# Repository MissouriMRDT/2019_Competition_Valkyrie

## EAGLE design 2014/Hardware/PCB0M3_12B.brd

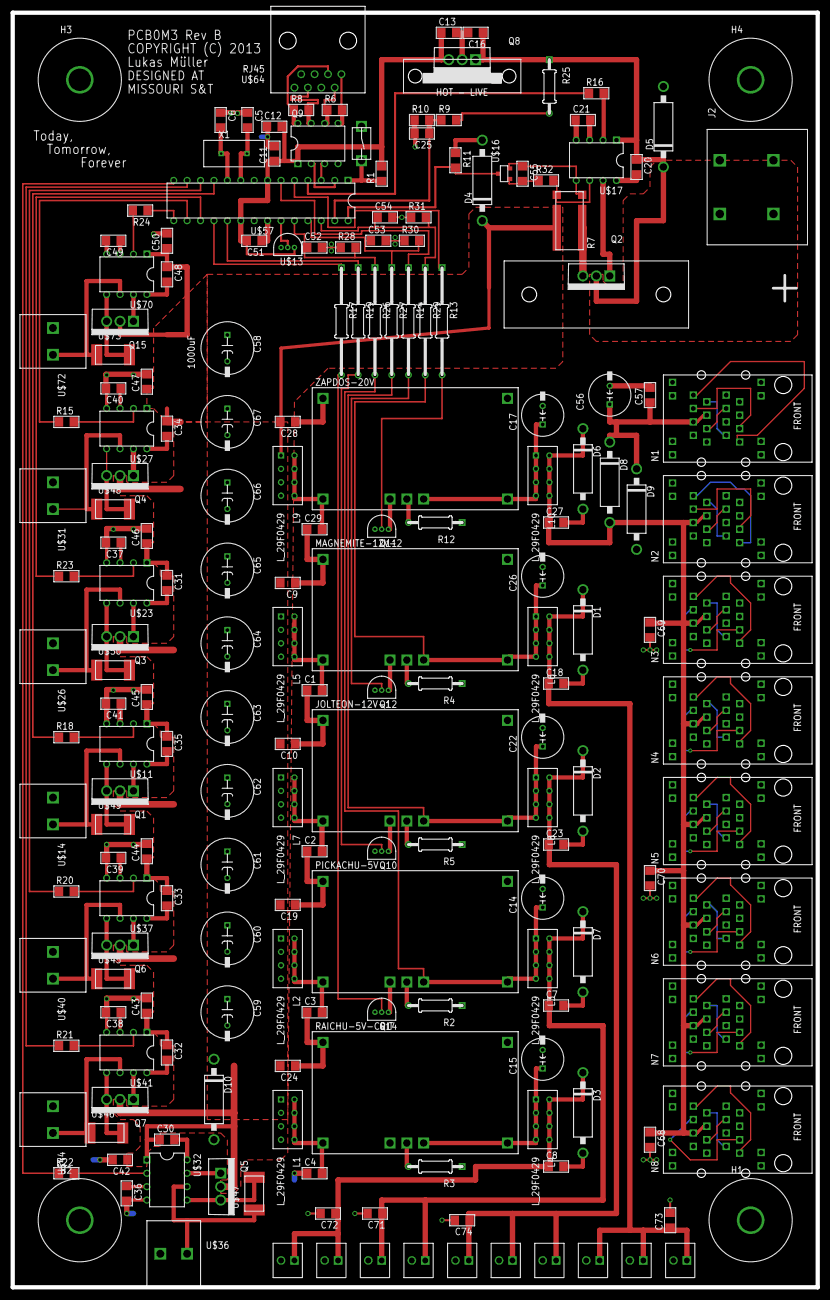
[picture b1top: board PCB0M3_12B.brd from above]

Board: 2 copper layers, 152.4 x 241.3 mm, 196 parts (0 on the bottom side), 143 nets.

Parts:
C1, C2, C3, C4, C5, C6, C11, C12, C13, C16, C20, C21, C25, C29, C30, C31, C32, C33, C34, C35, C36, C37, C38, C39, C40, C41, C42, C43, C44, C45, C46, C47, C48, C49, C50, C51, C52, C53, C54, C55, C57: C_1206
C7, C8, C9, C10, C18, C19, C23, C24, C27, C28, C68, C69, C70, C71, C72, C73, C74: 1uF; C_1206
C14, C15, C17, C22, C26, C56: C_POL8MM; C_8MM
C58: 1000uF; C_10MM
C59, C60, C61, C62, C63, C64, C65, C66, C67: C_10MM
D1, D2: 1.5KE13A-E3/54; DIODE_D3.5MM_LS15.24MM
D3, D7: ICTE5-E3/54; DIODE_D3.5MM_LS15.24MM
D4, D5, D10: 1.5KE30C-RH; DIODE_D3.5MM_LS15.24MM
D6: 1.5KE24CA-E3/73; DIODE_D3.5MM_LS15.24MM
D8, D9: SB530-E3/54; DIODE_D3.5MM_LS15.24MM
H1, H2, H3, H4: H_MNTHOLE_#8
J1: J_MC32857; J_TOGGLE
J2: 0399700102; J_2CONHC
J3, J4, J5, J6, J7, J8: J_1546074-2282834-2; J_2.54MM
JOLTEON-12V-1: PTN78020HAH; R_PDSS-T7
L1, L2, L3, L4, L5, L6, L7, L8, L9, L10: L_29F0429
MAGNEMITE-12V-2: PTN78020HAH; R_PDSS-T7
N1, N2, N3, N4, N5, N6, N7, N8: RJ45; RJ45-CAT5E-2PACK
PICKACHU-5V: PTN78020WAH; R_PDSS-T7
Q1, Q3, Q4, Q5, Q6, Q7, Q15: U_FDPF045N10A_TO-220F; TO220F
Q2: Q_IRFB7437PBF_HS; TO-220-531102B02500G
Q8: Q_LDOHEATSINK; TO220_6025DG
Q9: Q_LTC490; DIP8
Q10, Q11, Q12, Q14: Q_2N7000; TO-92-3
R1, R6, R8, R9, R10, R11, R15, R16, R18, R20, R21, R22, R23, R24, R28, R30, R31, R32: R_1206
R2, R3: 21k; R_1/4W
R4, R5: 242k; R_1/4W
R7: 0.001; R_FC4L
R12: 1.74k; R_1/4W
R13, R14, R17, R19, R26, R27, R29: R_1/4WL
R25: R_1/4W
RAICHU-5V-CRIT: PTN78020WAH; R_PDSS-T7
U$11, U$17, U$23, U$27, U$32, U$37, U$41, U$70: Q_MIC5021; DIP8
U$13: Q_LM35; TO-92-3
U$14, U$26, U$31, U$36, U$40, U$44, U$72: J_1546074-2; THERM_BLOCK_2
U$16: Q_ZXCT1109; SOT23
U$45, U$46, U$47, U$48, U$49, U$50, U$73: R_2512
U$52, U$53, U$54, U$55: J_1546074-2282834-2; J_2.54MM
U$57: Q_ATMEGA328P; DIP28
U$64: RJ45; RJ45-CAT5E
X1: HC49S; HC-49
ZAPDOS-20V: PTN78020HAH; R_PDSS-T7

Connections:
GND: C1.1, C2.1, C3.1, C4.1, C5.1, C6.1, C7.2, C8.2, C9.1, C10.1, C11.2, C12.1, C13.2, C14.-, C15.-, C16.2, C17.-, C18.2, C19.1, C21.1, C22.-, C23.2, C24.1, C25.2, C26.-, C27.2, C28.1, C29.1, C36.2, C37.2, C38.2, C39.2, C40.2, C41.2, C42.2, C43.2, C44.2, C45.2, C46.2, C47.2, C49.2, C50.2, C51.1, C52.2, C53.2, C54.2, C56.-, C57.2, C58.P$2, C59.P$2, C60.P$2, C61.P$2, C62.P$2, C63.P$2, C64.P$2, C65.P$2, C66.P$2, C67.P$2, C68.2, C69.2, C70.2, C71.2, C72.2, C73.2, C74.2, D1.A, D2.A, D3.A, D4.A, D5.A, D6.A, D7.A, D10.A, J1.P$1, J2.PIN2-1, J2.PIN2-2, J3.P$2, J4.P$2, J5.P$2, J6.P$2, J7.P$2, J8.P$2, JOLTEON-12V-1.1, JOLTEON-12V-1.7, MAGNEMITE-12V-2.1, MAGNEMITE-12V-2.7, N1.1-7, N1.1-8, N1.2-7, N1.2-8, N2.1-7, N2.1-8, N2.2-7, N2.2-8, N3.1-7, N3.1-8, N3.2-7, N3.2-8, N4.1-7, N4.1-8, N4.2-7, N4.2-8, N5.1-7, N5.1-8, N5.2-7, N5.2-8, N6.1-7, N6.1-8, N6.2-7, N6.2-8, N7.1-7, N7.1-8, N7.2-7, N7.2-8, N8.1-7, N8.1-8, N8.2-7, N8.2-8, PICKACHU-5V.1, PICKACHU-5V.7, Q8.2, Q9.4, Q10.1, Q11.1, Q12.1, Q14.1, R2.1, R3.1, R4.1, R5.1, R10.1, R11.1, R12.1, R28.1, R30.1, R31.1, RAICHU-5V-CRIT.1, RAICHU-5V-CRIT.7, U$11.4, U$13.1, U$14.P$2, U$17.4, U$23.4, U$26.P$2, U$27.4, U$31.P$2, U$32.4, U$36.P$2, U$37.4, U$40.P$2, U$41.4, U$44.P$2, U$52.P$2, U$53.P$2, U$54.P$2, U$55.P$2, U$57.8, U$57.22, U$64.7, U$64.8, U$70.4, U$72.P$2, ZAPDOS-20V.1, ZAPDOS-20V.7
M_IMAIN: R11.2, U$16.3, U$57.28
M_V5-2: C52.1, R26.1, R28.2, U$57.24
M_V12-1: C53.1, R27.1, R30.2, U$57.25
M_V12-2: C54.1, R29.1, R31.2, U$57.26
M_VMAIN: C25.1, R9.1, R10.2, U$57.27
unnamed: MAGNEMITE-12V-2.4, R4.2
unnamed: C26.+, L6.1, L6.2, L6.3, L6.4, MAGNEMITE-12V-2.5, MAGNEMITE-12V-2.6, R29.2
unnamed: Q14.2, R17.2
unnamed: JOLTEON-12V-1.4, R5.2
unnamed: C22.+, JOLTEON-12V-1.5, JOLTEON-12V-1.6, L8.1, L8.2, L8.3, L8.4, R27.2
unnamed: U$13.2, U$57.23
unnamed: N6.1-1, N6.2-1
unnamed: N6.1-2, N6.2-2
unnamed: N6.1-3, N6.2-3
unnamed: N6.1-6, N6.2-6
unnamed: N5.1-1, N5.2-1
unnamed: N5.1-2, N5.2-2
unnamed: N5.1-3, N5.2-3
unnamed: N5.1-6, N5.2-6
unnamed: N4.1-1, N4.2-1
unnamed: N4.1-2, N4.2-2
unnamed: N4.1-3, N4.2-3
unnamed: N4.1-6, N4.2-6
unnamed: N3.1-1, N3.2-1
unnamed: N3.1-2, N3.2-2
unnamed: N3.1-6, N3.2-6
unnamed: N2.1-1, N2.2-1
unnamed: N2.1-2, N2.2-2
unnamed: N2.1-3, N2.2-3
unnamed: N2.1-6, N2.2-6
unnamed: N1.1-1, N1.2-1
unnamed: N1.1-2, N1.2-2
unnamed: N1.1-3, N1.2-3
unnamed: N1.1-6, N1.2-6
unnamed: N3.1-3, N3.2-3
unnamed: N7.1-1, N7.2-1
unnamed: N7.1-2, N7.2-2
unnamed: N7.1-3, N7.2-3
unnamed: N7.1-6, N7.2-6
unnamed: N8.1-1, N8.2-1
unnamed: N8.1-2, N8.2-2
unnamed: N8.1-3, N8.2-3
unnamed: N8.1-6, N8.2-6
unnamed: Q1.3, U$11.5, U$49.P$2
unnamed: U$11.6, U$14.P$1, U$49.P$1
unnamed: Q1.1, U$11.7
unnamed: R18.2, U$11.2
unnamed: C35.2, U$11.8
unnamed: Q2.1, U$17.7
unnamed: Q2.3, R7.1
unnamed: C55.1, R7.SENSE1, U$16.2, U$17.5
unnamed: R16.2, U$17.2
unnamed: C21.2, U$17.3
unnamed: R3.2, RAICHU-5V-CRIT.4
unnamed: PICKACHU-5V.4, R2.2
unnamed: C55.2, R32.1, U$16.1
unnamed: Q3.3, U$23.5, U$50.P$2
unnamed: C14.+, L3.1, L3.2, L3.3, L3.4, PICKACHU-5V.5, PICKACHU-5V.6, R26.2
unnamed: C15.+, L4.1, L4.2, L4.3, L4.4, RAICHU-5V-CRIT.5, RAICHU-5V-CRIT.6
unnamed: U$23.6, U$26.P$1, U$50.P$1
unnamed: Q3.1, U$23.7
unnamed: C1.2, L5.5, L5.6, L5.7, L5.8, MAGNEMITE-12V-2.2
unnamed: R23.2, U$23.2
unnamed: C31.2, U$23.8
unnamed: Q4.3, U$27.5, U$48.P$2
unnamed: U$27.6, U$31.P$1, U$48.P$1
unnamed: Q4.1, U$27.7
unnamed: R15.2, U$27.2
unnamed: C34.2, U$27.8
unnamed: C3.2, L2.5, L2.6, L2.7, L2.8, PICKACHU-5V.2
unnamed: Q5.3, U$32.5, U$47.P$2
unnamed: U$32.6, U$36.P$1, U$47.P$1
unnamed: Q5.1, U$32.7
unnamed: R22.2, U$32.2
unnamed: C30.2, U$32.8
unnamed: Q6.3, U$37.5, U$45.P$2
unnamed: U$37.6, U$40.P$1, U$45.P$1
unnamed: Q6.1, U$37.7
unnamed: R20.2, U$37.2
unnamed: C33.2, U$37.8
unnamed: Q7.3, U$41.5, U$46.P$2
unnamed: U$41.6, U$44.P$1, U$46.P$1
unnamed: Q7.1, U$41.7
unnamed: R21.2, U$41.2
unnamed: C32.2, U$41.8
unnamed: Q15.3, U$70.5, U$73.P$2
unnamed: C5.2, U$57.9, X1.P$2
unnamed: C6.2, U$57.10, X1.P$1
unnamed: Q9.2, U$57.2
unnamed: R7.SENSE2, R32.2, U$17.6
unnamed: J1.P$2, R1.1, U$57.1
unnamed: Q9.3, U$57.3
unnamed: R12.2, ZAPDOS-20V.4
unnamed: Q9.5, R6.2, U$64.1
unnamed: Q9.6, R6.1, U$64.2
unnamed: Q9.7, R8.2, U$64.6
unnamed: R9.2, R25.2
unnamed: Q9.8, R8.1, U$64.3
unnamed: U$70.6, U$72.P$1, U$73.P$1
unnamed: C20.2, U$17.8
unnamed: C17.+, L10.1, L10.2, L10.3, L10.4, ZAPDOS-20V.5, ZAPDOS-20V.6
unnamed: C29.2, L9.5, L9.6, L9.7, L9.8, ZAPDOS-20V.2
unnamed: JOLTEON-12V-1.3, Q10.3
unnamed: MAGNEMITE-12V-2.3, Q12.3
unnamed: Q11.3, ZAPDOS-20V.3
unnamed: PICKACHU-5V.3, Q14.3
unnamed: C41.1, U$11.3
unnamed: C37.1, U$23.3
unnamed: C36.1, U$32.3
unnamed: C38.1, U$41.3
unnamed: C39.1, U$37.3
unnamed: C40.1, U$27.3
unnamed: C2.2, JOLTEON-12V-1.2, L7.5, L7.6, L7.7, L7.8
unnamed: Q11.2, R13.2
unnamed: C4.2, L1.5, L1.6, L1.7, L1.8, RAICHU-5V-CRIT.2
unnamed: Q10.2, R19.2
unnamed: Q12.2, R14.2
unnamed: Q15.1, U$70.7
unnamed: C48.2, U$70.8
unnamed: C49.1, U$70.3
unnamed: R24.2, U$70.2
S_12V-2: R14.1, U$57.6
S_MAIN: R16.1, U$57.4
S_MC1: R22.1, U$57.14
S_MC2: R21.1, U$57.13
S_MC3: R20.1, U$57.12
S_MC4: R18.1, U$57.11
S_MC5: R15.1, U$57.16
S_MC6: R23.1, U$57.17
S_POE: R13.1, U$57.5
S_V5-2: R17.1, U$57.18
S_V12-1: R19.1, U$57.19
S_V24AUX: R24.1, U$57.15
V1: C16.1, C20.1, D5.C, J2.PIN1-1, J2.PIN1-2, Q2.2, Q8.1, R25.1, U$17.1
V5-CRT: C8.1, C72.1, D3.C, L4.5, L4.6, L4.7, L4.8, U$52.P$1, U$53.P$1
V12: C7.1, C71.1, D7.C, L3.5, L3.6, L3.7, L3.8, U$54.P$1, U$55.P$1
V15_1: C18.1, C73.1, D1.C, J6.P$1, J7.P$1, J8.P$1, L6.5, L6.6, L6.7, L6.8
V15_2: C23.1, C74.1, D2.C, J3.P$1, J4.P$1, J5.P$1, L8.5, L8.6, L8.7, L8.8
V24: C9.2, C10.2, C19.2, C24.2, C28.2, C30.1, C31.1, C32.1, C33.1, C34.1, C35.1, C42.1, C43.1, C44.1, C45.1, C46.1, C47.1, C48.1, C50.1, C58.P$1, C59.P$1, C60.P$1, C61.P$1, C62.P$1, C63.P$1, C64.P$1, C65.P$1, C66.P$1, C67.P$1, D4.C, D10.C, L1.1, L1.2, L1.3, L1.4, L2.1, L2.2, L2.3, L2.4, L5.1, L5.2, L5.3, L5.4, L7.1, L7.2, L7.3, L7.4, L9.1, L9.2, L9.3, L9.4, Q1.2, Q3.2, Q4.2, Q5.2, Q6.2, Q7.2, Q15.2, R7.2, U$11.1, U$23.1, U$27.1, U$32.1, U$37.1, U$41.1, U$70.1
VA5: C11.1, C12.2, C13.1, C51.2, Q8.3, Q9.1, R1.2, U$13.3, U$57.7, U$57.20
V_ANTENNA: C56.+, C57.1, D8.C, D9.C, N1.1-4, N1.1-5
V_POE: C27.1, C68.1, C69.1, C70.1, D6.C, D8.A, L10.5, L10.6, L10.7, L10.8, N2.1-4, N2.1-5, N3.1-4, N3.1-5, N4.1-4, N4.1-5, N5.1-4, N5.1-5, N6.1-4, N6.1-5, N7.1-4, N7.1-5, N8.1-4, N8.1-5

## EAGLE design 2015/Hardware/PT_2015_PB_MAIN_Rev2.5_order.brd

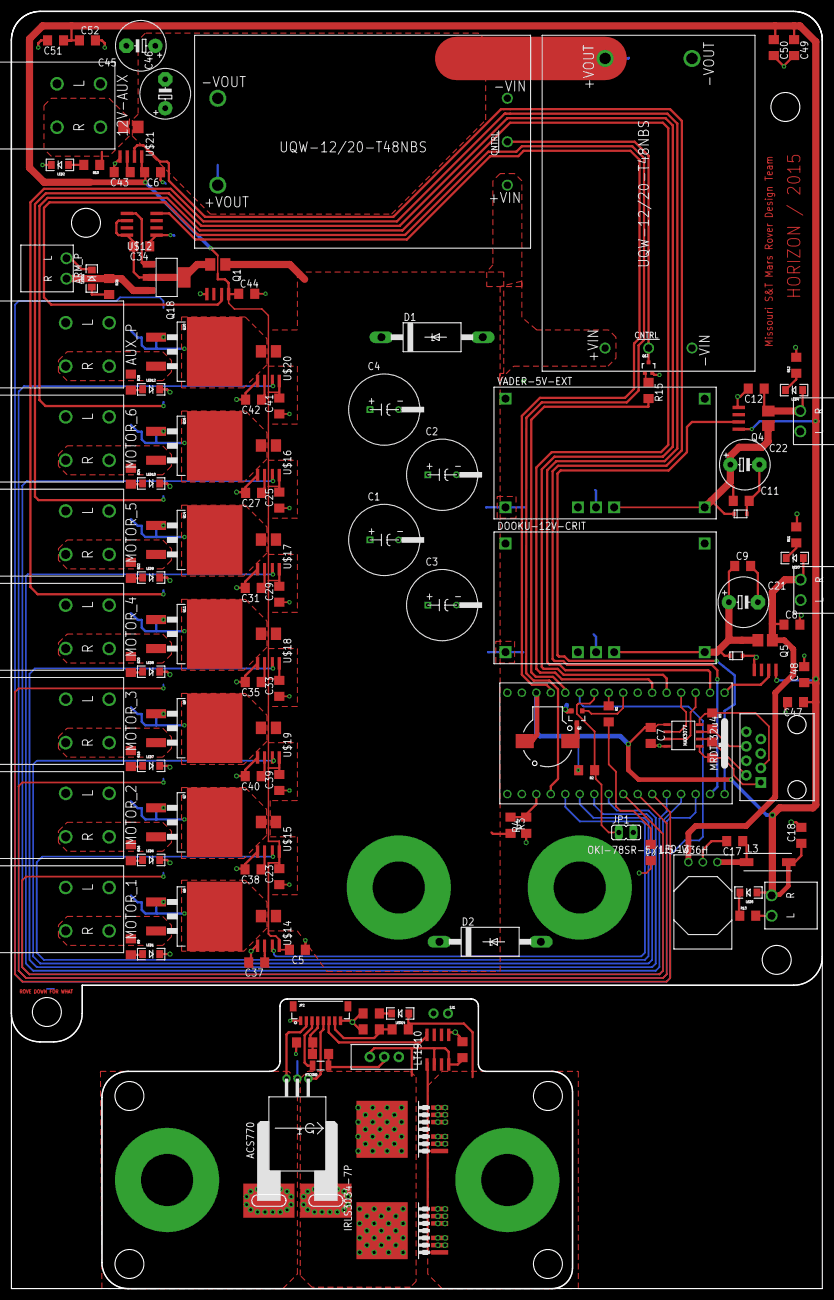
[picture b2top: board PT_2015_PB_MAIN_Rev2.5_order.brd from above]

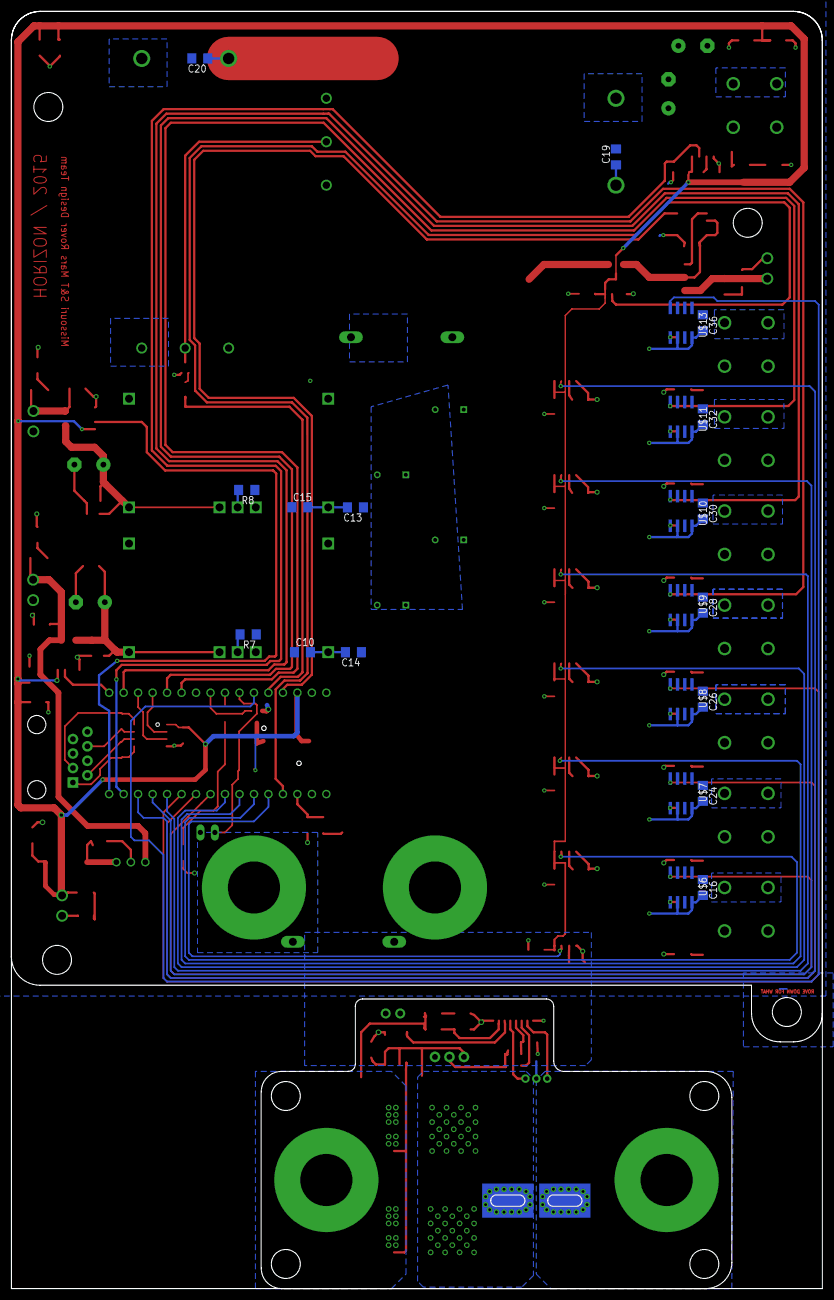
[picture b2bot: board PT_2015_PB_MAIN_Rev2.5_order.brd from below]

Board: 2 copper layers, 142.2 x 224.0 mm, 162 parts (22 on the bottom side), 103 nets.

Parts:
5V-EXT, 5V-INT, 12V-CRIT: H_WR-TBL_321*0002HORIZ; 691322110002
12V-AUX: H_20020618-M02HORIZ; 20020618-M02
ARM_P: H_WR-TBL_321*0002HORIZ; 691322110002
AUX_P: H_20020618-M02HORIZ; 20020618-M02
BATT-NEG: TERMINAL_HOLE; LARGE_TERMINAL_HOLE
BATT-POS: TERMINAL_HOLE; LARGE_TERMINAL_HOLE
C1, C2, C3, C4: 1mF; C_12.5MM
C5, C6, C23, C25, C29, C33, C39, C41, C44: .1µF; C1206
C7: 1uF; C1206
C8: 10µf; C1206
C9, C11, C48, C50, C52: 10uF; C1206
C10, C15, C16, C24, C26, C28, C30, C32, C34, C36, C53: 10µF; C1206
C12: 47µf; C1206
C13, C14: 1µF; C1206
C17, C18: 47µF; C1206
C19, C20: 47uF; C1206
C21, C22, C45, C46: 330µF; E5-8,5
C27, C31, C35, C37, C38, C40, C42, C43, C47, C49, C51: 1nF; C1206
D1, D2: 1.5KE36A; CB429-17
DOOKU-12V-CRIT: Q_PTN78020WAH; R_PDSS-T7
F1: PTCSMD; PTC-1206
IRLS3034-7P, IRLS3034-7P.2: D2PAK-7
JP1: JP1
JP2: BM08B-SRSS-TB
L3: L8530M
LED1, LED2, LED3, LED4, LED5, LED6, LED7, LED8, LED9, LED10, LED11, LED12, LED14: LED-1206
LED13: FKIT-LED-1206
MOTOR_1, MOTOR_2, MOTOR_3, MOTOR_4, MOTOR_5, MOTOR_6: H_20020618-M02HORIZ; 20020618-M02
OKI-78SR-5/1.5-W36H: Q_OKI-78SR; OKI-78SRH
PALPATINE-12V: UQW-12/20-T48NBS; U-T48-QB-NO_TRIM
Q1: Q_ACS711LC_SKETCH; SOIC8_ACS711_SKETCH
Q2: 200mA/50V; SOT23-3
Q4, Q5: Q_ACS711LC; SOIC8_ACS711
Q6, Q7, Q9, Q11, Q14, Q16, Q20: Q_IRFS7437PbF; D2PACK
Q12: 2N7002; SOT323
Q18: Q_FDT86102LZ; SOT-223
R1: 1k Ohm; 1206
R2: 10k Ohm; 1206
R3, R14, R19: 60kΩ; R1206
R4, R17, R21: 10kΩ; R1206
R5, R6: 120 Ohm; 1206
R7: 590Ω; R1206
R8: 21kΩ; R1206
R9, R16, R18, R20, R22, R24, R26, R28: 5kΩ; 1206
R10, R11: 1kΩ; 1206
R12, R13: 330; 1206
R15: 1k; R1206
R23: 5kΩ; R1206
S1: SWITCH-SPDT
SG1: BUZZERSMD2; BUZZER-CCV
SIDEOUS-12V: UQW-12/20-T48NBS; U-T48-QB-NO_TRIM
SJ1: GROUND TIE; PTH-JUMPER-2-NO_NO_SILK
U$1: 32U4_BREAKOUT; 32U4_MCU_DIP
U$2, U$5: D_SD12T1G; SOD-323
U$3: MAX3077; MAX3070E
U$4: RJ45-8PTH; RJ45-8
U$6, U$7, U$8, U$9, U$10, U$11, U$12, U$13, U$24: LT1910; SO8
U$14, U$15, U$16, U$17, U$18, U$19, U$20: ACS714LLCTR-50A-T; SOIC8_ACS711_SKETCH
U$21: ACS714LLCTR-50A-T; SOIC8_ACS711
U$22: TEST
U$23: ACS770; PFF_LEADFORM
VADER-5V-EXT: Q_PTN78020WAH; R_PDSS-T7
V_ARRAY: TERMINAL_HOLE; LARGE_TERMINAL_HOLE
V_OUT: TERMINAL_HOLE; LARGE_TERMINAL_HOLE

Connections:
5V: JP2.5, U$23.1
5V-EXT: 5V-EXT.R, C12.1, LED4.A, Q4.4
5V-IMEAS: Q4.7, U$1.32
12V-AUX: 12V-AUX.R1, 12V-AUX.R2, R10.1, U$21.4
12V-CRIT: 12V-CRIT.R, C8.1, LED3.A, OKI-78SR-5/1.5-W36H.1, Q5.1
12V-IMEAS: U$1.31, U$21.7
12V-SIG: R15.2, U$1.12
+5V: 5V-INT.R, C5.2, C6.2, C7.1, C18.1, C23.2, C25.2, C29.2, C33.2, C39.2, C41.2, C44.1, C47.1, C48.1, C49.1, C50.1, C51.1, C52.1, L3.2, LED5.A, Q1.8, Q4.8, Q5.8, R2.2, SG1.+, U$1.14, U$3.VCC, U$14.8, U$15.8, U$16.8, U$17.8, U$18.8, U$19.8, U$20.8, U$21.8
ARM_P-IMEAS: Q1.7, U$1.20
ARM_P-SIG: U$1.13, U$12.4
AUX_P-IMEAS: U$1.30, U$20.7
AUX_P-SIG: U$1.11, U$13.4
BUZZ_BUZZ_MOTHERFUCKER: Q2.1, U$1.8
CRIT-IMEAS: Q5.7, U$1.1
GATE: JP2.6, U$24.4
GND: 5V-EXT.L, 5V-INT.L, 12V-AUX.L1, 12V-AUX.L2, 12V-CRIT.L, ARM_P.L, AUX_P.L1, AUX_P.L2, BATT-NEG.P$1, C1.-, C2.-, C3.-, C4.-, C5.1, C6.1, C7.2, C8.2, C9.2, C10.1, C11.2, C12.2, C13.1, C14.1, C15.1, C16.1, C17.2, C18.2, C19.2, C20.2, C21.-, C22.-, C23.1, C24.1, C25.1, C26.1, C27.2, C28.1, C29.1, C30.1, C31.2, C32.1, C33.1, C34.1, C35.2, C36.1, C37.2, C38.2, C39.1, C40.2, C41.1, C42.2, C43.2, C44.2, C45.-, C46.-, C47.2, C48.2, C49.2, C50.2, C51.2, C52.2, D1.A, D2.A, DOOKU-12V-CRIT.1, DOOKU-12V-CRIT.7, JP1.2, LED1.C, LED2.C, LED6.C, LED7.C, LED8.C, LED9.C, LED10.C, LED11.C, LED12.C, LED13.C, MOTOR_1.L1, MOTOR_1.L2, MOTOR_2.L1, MOTOR_2.L2, MOTOR_3.L1, MOTOR_3.L2, MOTOR_4.L1, MOTOR_4.L2, MOTOR_5.L1, MOTOR_5.L2, MOTOR_6.L1, MOTOR_6.L2, OKI-78SR-5/1.5-W36H.2, PALPATINE-12V.3, PALPATINE-12V.4, Q1.5, Q2.2, Q4.5, Q5.5, Q12.2, R4.1, R7.1, R8.1, R11.2, R12.2, R13.2, SIDEOUS-12V.3, SIDEOUS-12V.4, U$1.15, U$1.17, U$2.2, U$3.GND, U$4.7, U$4.8, U$5.2, U$6.1, U$7.1, U$8.1, U$9.1, U$10.1, U$11.1, U$12.1, U$13.1, U$14.5, U$15.5, U$16.5, U$17.5, U$18.5, U$19.5, U$20.5, U$21.5, VADER-5V-EXT.1, VADER-5V-EXT.7
GND1: C53.2, JP2.1, JP2.8, R17.2, R21.1, R23.2, S1.3, SJ1.1, SJ1.2, U$23.2, U$24.1
INFO_LED: R1.1, U$1.9
I_ARRAY: JP2.2, U$23.3
JUMPER_SIG_IN: JP1.1, R2.1, U$1.10
LOGIC_POWER: F1.2, JP2.3
M1-IMEAS: U$1.21, U$14.7
M1-SIG: U$1.25, U$6.4
M2-IMEAS: U$1.22, U$15.7
M2-SIG: U$1.26, U$7.4
M3-IMEAS: U$1.23, U$19.7
M3-SIG: U$1.27, U$8.4
M4-IMEAS: U$1.24, U$18.7
M4-SIG: U$1.2, U$9.4
M5-IMEAS: U$1.28, U$17.7
M5-SIG: U$1.5, U$10.4
M6-IMEAS: U$1.29, U$16.7
M6-SIG: U$1.6, U$11.4
unnamed: C37.1, U$14.6
unnamed: C38.1, U$15.6
unnamed: LED3.C, R11.1
unnamed: PALPATINE-12V.2, Q12.3, SIDEOUS-12V.2
unnamed: LED4.C, R12.1
unnamed: LED5.C, R13.1
unnamed: C19.1, C20.1, C45.+, C46.+, PALPATINE-12V.8, SIDEOUS-12V.8, U$21.1
unnamed: Q2.3, SG1.-
unnamed: DOOKU-12V-CRIT.4, R7.2
unnamed: IRLS3034-7P.2, IRLS3034-7P.3, IRLS3034-7P.4, IRLS3034-7P.5, IRLS3034-7P.6, IRLS3034-7P.2.2, IRLS3034-7P.2.3, IRLS3034-7P.2.4, IRLS3034-7P.2.5, IRLS3034-7P.2.6, LED14.A, R14.1, V_OUT.P$1
unnamed: LED13.A, R1.2
unnamed: C43.1, U$21.6
unnamed: R6.2, U$3.Y, U$4.1
unnamed: IRLS3034-7P.1, IRLS3034-7P.2.1, U$24.5
unnamed: C11.1, C22.+, Q4.1, U$2.1, VADER-5V-EXT.5, VADER-5V-EXT.6
unnamed: C27.1, U$16.6
unnamed: R6.1, U$3.Z, U$4.2
unnamed: R5.2, U$3.B, U$4.6
unnamed: R5.1, U$3.A, U$4.3
unnamed: U$1.3, U$3.DI
unnamed: C31.1, U$17.6
unnamed: C35.1, U$18.6
unnamed: C40.1, U$19.6
unnamed: C42.1, U$20.6
unnamed: C24.2, Q7.TAB, U$7.6, U$7.8, U$15.4
unnamed: MOTOR_2.R1, MOTOR_2.R2, Q7.2, R16.1
unnamed: Q7.1, U$7.5
unnamed: LED6.A, R16.2
unnamed: C53.1, IRLS3034-7P.PAD, IRLS3034-7P.2.PAD, S1.1, U$23.5_1, U$23.5_2, U$23.5_3, U$23.5_4, U$23.5_5, U$23.5_6, U$23.5_7, U$23.5_8, U$23.5_9, U$23.5_10, U$23.5_11, U$23.5_12, U$23.5_13, U$23.5_14, U$23.5_15, U$23.5_16, U$23.5_B, U$23.5_T, U$24.6, U$24.8
unnamed: U$23.4_1, U$23.4_2, U$23.4_3, U$23.4_4, U$23.4_5, U$23.4_6, U$23.4_7, U$23.4_8, U$23.4_9, U$23.4_10, U$23.4_11, U$23.4_12, U$23.4_13, U$23.4_14, U$23.4_15, U$23.4_16, U$23.4_B, U$23.4_T, V_ARRAY.P$1
unnamed: F1.1, R19.2, S1.2
unnamed: R8.2, VADER-5V-EXT.4
unnamed: C9.1, C21.+, DOOKU-12V-CRIT.5, DOOKU-12V-CRIT.6, Q5.4, U$5.1
unnamed: LED14.C, R23.1
unnamed: LED1.A, R9.2
unnamed: C16.2, Q6.TAB, U$6.6, U$6.8, U$14.4
unnamed: MOTOR_1.R1, MOTOR_1.R2, Q6.2, R9.1
unnamed: Q6.1, U$6.5
unnamed: C26.2, Q9.TAB, U$8.6, U$8.8, U$19.4
unnamed: MOTOR_3.R1, MOTOR_3.R2, Q9.2, R18.1
unnamed: LED2.A, R10.2
unnamed: Q9.1, U$8.5
unnamed: LED7.A, R18.2
unnamed: C28.2, Q11.TAB, U$9.6, U$9.8, U$18.4
unnamed: Q11.1, U$9.5
unnamed: LED8.A, R20.2
unnamed: C30.2, Q14.TAB, U$10.6, U$10.8, U$17.4
unnamed: MOTOR_5.R1, MOTOR_5.R2, Q14.2, R22.1
unnamed: Q14.1, U$10.5
unnamed: LED9.A, R22.2
unnamed: C32.2, Q16.TAB, U$11.6, U$11.8, U$16.4
unnamed: MOTOR_6.R1, MOTOR_6.R2, Q16.2, R24.1
unnamed: Q16.1, U$11.5
unnamed: LED10.A, R24.2
unnamed: C34.2, Q1.4, Q18.2, Q18.4, U$12.6, U$12.8
unnamed: ARM_P.R, Q18.3, R26.1
unnamed: Q18.1, U$12.5
unnamed: LED11.A, R26.2
unnamed: C36.2, Q20.TAB, U$13.6, U$13.8, U$20.4
unnamed: AUX_P.R1, AUX_P.R2, Q20.2, R28.1
unnamed: Q20.1, U$13.5
unnamed: LED12.A, R28.2
unnamed: C17.1, L3.1, OKI-78SR-5/1.5-W36H.3
unnamed: Q12.1, R15.1
PRIMARY-VMEAS: R3.1, R4.2, U$1.19
RXD: U$1.4, U$3.RO
U: MOTOR_4.R1, MOTOR_4.R2, Q11.2, R20.1
V_BATT: BATT-POS.P$1, C1.+, C2.+, C3.+, C4.+, C10.2, C13.2, C14.2, C15.2, D1.C, D2.C, DOOKU-12V-CRIT.2, PALPATINE-12V.1, Q1.1, R3.2, SIDEOUS-12V.1, U$14.1, U$15.1, U$16.1, U$17.1, U$18.1, U$19.1, U$20.1, VADER-5V-EXT.2
V_CHECK: JP2.4, R19.1, R21.2
V_OUT: JP2.7, R14.2, R17.1

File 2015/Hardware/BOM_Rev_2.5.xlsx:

Qty | Value | Device | Package | Parts | Description | DIGIKEY_PN | PROD_ID | VALUE
1 | We have these | Ferrite Bead | L8530M | L3 | INDUCTOR, American symbol | We already have them
13 | LED | LED | LED-1206 | LED1, LED2, LED3, LED4, LED5, LED6, LED7, LED8, LED9, LED10, LED11, LED12, LED13 | LEDs | 754-1171-1-ND
9 | .1µF | Capacitor | C1206 | C5, C6, C23, C25, C29, C33, C39, C41, C44 | CAPACITOR, American symbol | 399-1249-1-ND
2 | 1.5KE36A | TVS Diode | CB429-17 | D1, D2 | DIODE | 1.5KE36A-TPMSCT-ND | Should have plenty
1 | 10k Ohm | Resistor | R1206 | R2, R4 | RESISTOR, American symbol | P10.0KFCT-ND
16 | 10 µF | Capacitor | C1206 | C10, C15, C16, C24, C26, C28, C30, C32, C34, C36, C8, C9, C11, C48, C50, C52 | CAPACITOR, American symbol | 587-3248-1-ND
2 | 120 Ohm | Resistor | 1206 | R5, R6 | Resistor | P120FCT-ND | Should have plenty
4 | 1k Ohm | Resistor | 1206 | R10, R11, R1, R15 | Resistor | P1.00KFCT-ND | Should have plenty
4 | 1mF | Capacitor | C_12.5MM | C1, C2, C3, C4 | Alum Elect. Cap with 10mm diameter, 5mm lead spacing and 0.7mm lead diameter | UVY1H102MHD-ND | Should have plenty
11 | 1nF | Capacitor | C1206 | C27, C31, C35, C37, C38, C40, C42, C43, C47, C49, C51 | CAPACITOR, American symbol | 399-1147-1-ND
2 | 1 µF | Capacitor | C1206 | C7, C13, C14 | CAPACITOR, American symbol | 445-1423-1-ND
1 | 200mA/50V | Small MOSFET | SOT23-3 | Q2 | Common NMOSFET Parts | BSS138CT-ND | TRANS-00830 | 200mA/50V
1 | 21k Ohm | Resistor | R1206 | R8 | RESISTOR, American symbol | P21.0KFCT-ND
1 | 2N7002 | Small MOSFET | SOT323 | Q12 | Common NMOSFET Parts | 2N7002WT1GOSCT-ND | TRANS-11151
1 | 32U4_BREAKOUT | 32U4_BREAKOUT | 32U4_MCU_DIP | U$1
2 | 330 Ohm | Resistor | 1206 | R12, R13 | Resistor | RHM330CJCT-ND
4 | 330µF | Capacitor | E5-8,5 | C21, C22, C45, C46 | POLARIZED CAPACITOR, American symbol | 493-1042-ND
5 | 47uF | Capacitor | C1206 | C19, C20, C17, C18, C12 | CAPACITOR, American symbol | 490-9967-1-ND
1 | 590 Ohm | Resistor | R1206 | R7 | RESISTOR, American symbol | P590FCT-ND
8 | 5k ohm | Resistor | 1206 | R9, R16, R18, R20, R22, R24, R26, R28 | Resistor | 541-5.1KECT-ND
1 | 60k ohm | Resistor | R1206 | R3 | RESISTOR, American symbol | P60.4KFCT-ND
8 | ACS714LLCTR-50A-T | Current Sensor | SOIC8_ACS711 | U$21, U$14, U$15, U$16, U$17, U$18, U$19, U$20 | Sketch variant has increased clearance for traces. | 620-1683-1-ND
1 | BUZZERSMD2 | Buzzer | BUZZER-CCV | SG1 | Buzzer 12mm
1 | D_SD12T1G | 5V TVS Zener Diode | SOD-323 | U$2 | 5V Zener | SD05T1GOSCT-ND
1 | D_SD12T1G | 12V TVS Zener Diode | SOD-323 | U$5 | 12V Zener | SD12T1GOSCT-ND
8 | H_20020618-M02HORIZ | 30A Terminal | 20020618-M02 | 12V-AUX, AUX_P, MOTOR_1, MOTOR_2, MOTOR_3, MOTOR_4, MOTOR_5, MOTOR_6 | High amp pluggable screw terminal from FCI. Rated up to 32A | 609-3951-ND | Should have plenty
4 | H_WR-TBL_321*0002HORIZ | 10A Terminal | 691322110002 | 5V-EXT, 5V-INT, 12V-CRIT, ARM_P | Wurth Electronic's 2-pin 10A pluggable screw terminal headers. Vertical and Hor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 | 732-2769-ND
8 | LT1910 | MOSFET Driver | SO8 | U$6, U$7, U$8, U$9, U$10, U$11, U$12, U$13 |  | LT1910IS8#PBF-ND | Buy extra
1 | MAX3077 | RS-485 Transeiver | MAX3070E | U$3
3 | Q_ACS711LC | Current Sensor | SOIC8_ACS711 | Q1, Q4, Q5 | Â±12.5A or Â±25A Hall-effect current transducer. SOIC-8 Package with fused pads. | 620-1372-1-ND
1 | Q_FDT86102LZ | MOSFET | SOT-223 | Q18 |  | FDT86102LZFSCT-ND
7 | Q_IRFS7437PbF | MOSFET | D2PACK | Q6, Q7, Q9, Q11, Q14, Q16, Q20 | 40V 195A N-CH MOSFET switch with heatsink | IRFS7437PBF-ND | Buy extra
1 | Q_OKI-78SR | Board-Mount Power Electronic Converter | OKI-78SRH | OKI-78SR-5/1.5-W36H | 4.95W DC/DC Converter | 811-2692-ND
2 | Q_PTN78020WAH | Board-Mount Power Electronic Converter | R_PDSS-T7 | DOOKU-12V-CRIT, VADER-5V-EXT | TI DC/DC converter 36Vin - Adjustable output | 296-20515-ND
1 | RJ45-8PTH | RJ45 Jack | RJ45-8 | U$4 | RJ45 Jack |  | should have plenty
2 | UQW-12/20-T48NBS | Board-Mount Power Electronic Converter | U-T48-QB-NO_TRIM | PALPATINE-12V, SIDEOUS-12V | Murata 12V DC/DC Converter- 20 Amp | 811-2966-ND

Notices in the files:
2014/Hardware/PCB0M3_12B.brd:
COPYRIGHT (C) 2013
parts and their libraries:
SparkFun-Connectors: Licensing: CC v3.0 Share-Alike You are welcome to use this library for commercial purposes.
SparkFun-LED: Licensing: Creative Commons ShareAlike 4.0 International - https://creativecommons.org/licenses/by-sa/4.0
